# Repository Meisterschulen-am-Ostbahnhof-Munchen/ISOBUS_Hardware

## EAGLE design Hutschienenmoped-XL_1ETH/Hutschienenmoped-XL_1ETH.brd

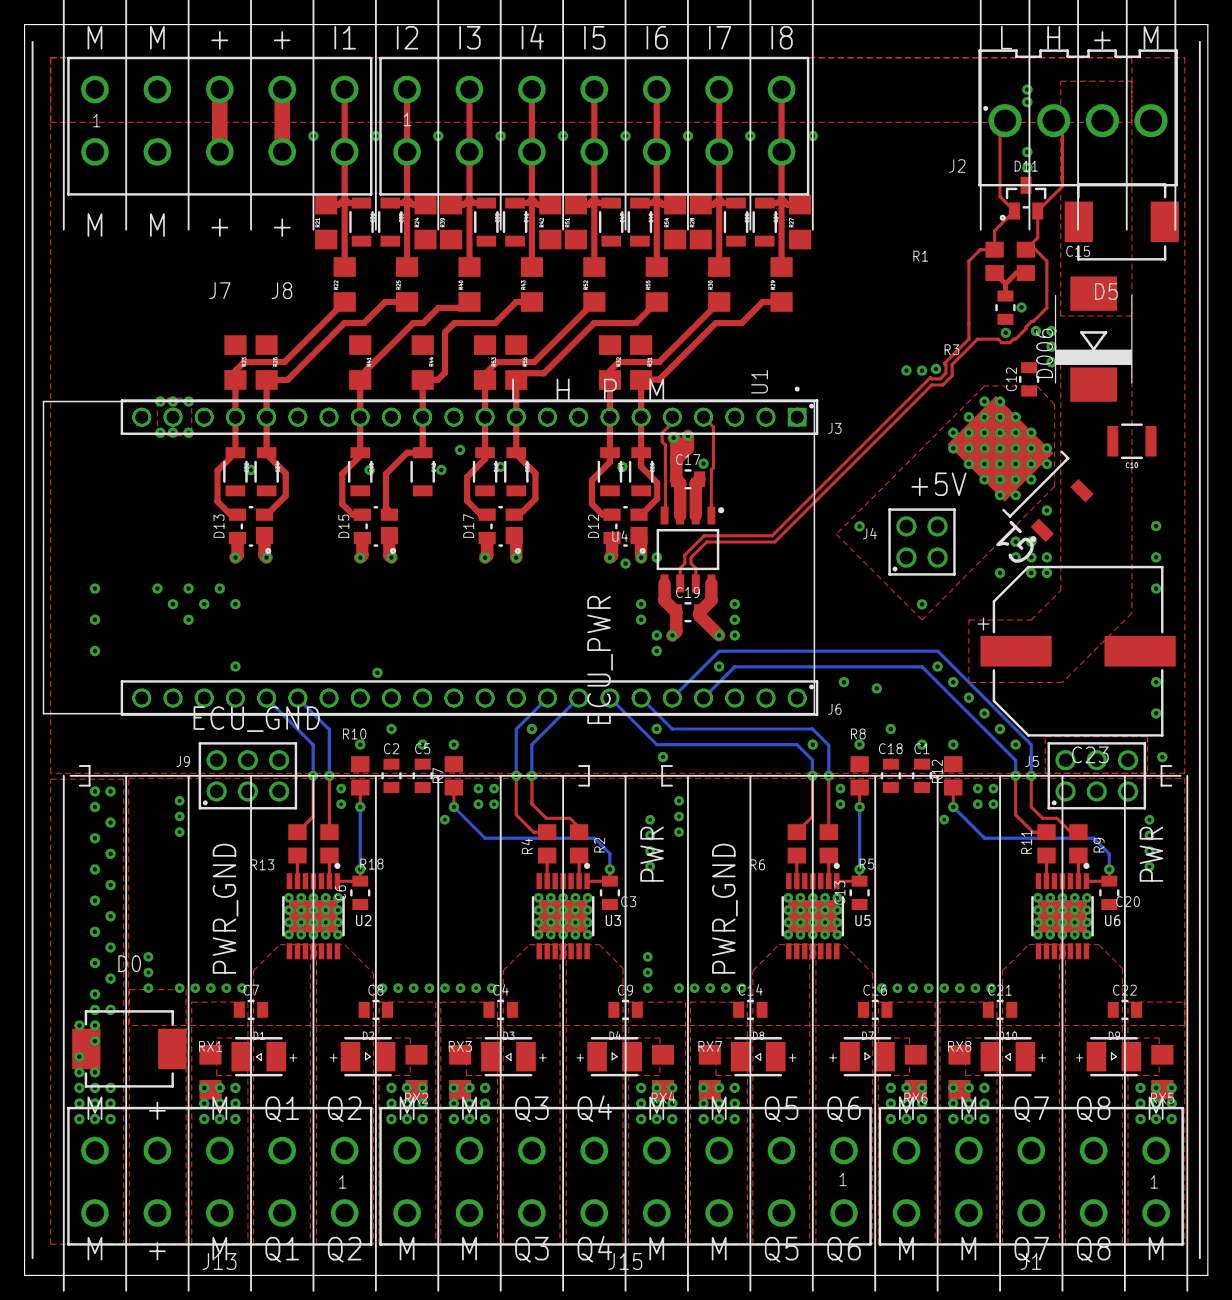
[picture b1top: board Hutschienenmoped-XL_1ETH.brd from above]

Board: 4 copper layers, 96.3 x 101.8 mm, 118 parts (0 on the bottom side), 65 nets.

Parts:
C1, C2, C3, C5, C6, C13, C17, C18, C19, C20: 100nF; WCAP-CSGP_0805_H0.8_R
C4, C7, C8, C9, C14, C16, C21, C22: 10nF; WCAP-CSGP_0805_H0.8_R
C10: 22uF; WCAP-CSGP_1210_H2.5
C12: 22uF; WCAP-CSGP_0805_H1.25_R
C15: 47nF; WCAP-CSGP_0805_H0.8_R
C23: 330 µF; WCAP-ASLI_12.5X14(DXL)
C24, C25, C26, C27, C31, C32, C33, C34, C39, C40, C41, C42, C47, C48, C49, C50: 100nF; WCAP-CSGP_1206_H0.8
D0, D5: 33V; WE-TVSP_DO-214AB_BIDIRECTIONAL
D1, D2, D3, D4, D7, D8, D9, D10: 150141VS73100; WL-SMTW_3528
D006: MBRS340T3; SMC
D11: 24Vdc; WE-TVS_SOT23-3L
D12, D13, D15, D17: 3.3Vdc; WE-TVS_SOT143-4L
G1: INF-PG-TO252-3-11_N
J1, J7, J13: 638207222005
J2: 645004114822
J3, J6: 61302211821
J4: 61300421121
J5, J9: 61300621121
J8: 638207222007
J15: 638207222008
R1, R3: 60R; R0805
R2, R4, R5, R6, R9, R11, R13, R18: 4k7; R0805
R7, R8, R10, R12: 47R; R0805
R21, R24, R27, R28, R39, R42, R51, R54: 1K2; R1206
R22, R25, R29, R30, R40, R43, R52, R55: 47K; R1206
R23, R26, R31, R32, R41, R44, R53, R56: 13K; R1206
RX1, RX2, RX3, RX4, RX5, RX6, RX7, RX8: 470Ohm; R1206
U1: ESP32-S3-DEVKITC-1-N8R2; XCVR_ESP32-S3-DEVKITC-1-N8R2
U2, U3, U5, U6: SOP65P600X115-15N-V
U4: TLE9250VSJ; SOIC127P602X173-8N-V

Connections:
+3V3: C19.1, D12.4, D13.4, D15.4, D17.4, U1.J1_1, U1.J1_2, U4.5
+5V: C12.2, C17.1, G1.2, J4.1, J4.2, J4.3, J4.4, U1.J1_21, U4.3
+6V: D7.1, RX6.1
AGNDU2: C6.2, R10.2, U2.1
AGNDU3: C3.2, R7.2, U3.1
AGNDU4: C13.2, R8.2, U5.1
AGNDU5: C20.2, R12.2, U6.1
CAN1_RXD: U1.J1_5, U4.4
CAN1_TXD: U1.J1_4, U4.1
CAN_N: D11.1, J2.1, R3.2, U4.6
CAN_P: D11.2, J2.2, R1.2, U4.7
CI1: C32.1, D13.3, R22.1, R23.2, U1.J1_19
CI2: C34.1, D13.2, R25.1, R26.2, U1.J1_18
CI3: C40.1, D15.3, R40.1, R41.2, U1.J1_15
CI4: C42.1, D15.2, R43.1, R44.2, U1.J1_13
CI5: C48.1, D17.3, R52.1, R53.2, U1.J1_11
CI6: C50.1, D17.2, R55.1, R56.2, U1.J1_10
CI7: C27.1, D12.3, R30.1, R32.2, U1.J1_7
CI8: C26.1, D12.2, R29.1, R31.2, U1.J1_6
ECU_GND: C1.2, C2.2, C5.2, C10.1, C12.1, C15.2, C17.2, C18.2, C19.2, C23.2, C24.2, C25.2, C26.2, C27.2, C31.2, C32.2, C33.2, C34.2, C39.2, C40.2, C41.2, C42.2, C47.2, C48.2, C49.2, C50.2, D5.1, D11.3, D12.1, D13.1, D15.1, D17.1, G1.1, J2.4, J7.1, J7.2, J7.A1, J7.A2, J9.2, J9.4, J9.6, R7.1, R8.1, R10.1, R12.1, R21.1, R23.1, R24.1, R26.1, R27.1, R28.1, R31.1, R32.1, R39.1, R41.1, R42.1, R44.1, R51.1, R53.1, R54.1, R56.1, U1.J1_22, U1.J3_1, U1.J3_21, U1.J3_22, U4.2, U4.8
ECU_PWR: D5.2, D006.A, J2.3, J5.2, J5.4, J5.6, J7.3, J7.4, J7.A3, J7.A4
I1: C31.1, J7.5, J7.A5, R21.2, R22.2
I2: C33.1, J8.1, J8.A1, R24.2, R25.2
I3: C39.1, J8.2, J8.A2, R39.2, R40.2
I4: C41.1, J8.3, J8.A3, R42.2, R43.2
I5: C47.1, J8.4, J8.A4, R51.2, R52.2
I6: C49.1, J8.5, J8.A5, R54.2, R55.2
I7: C25.1, J8.6, J8.A6, R28.2, R30.2
I8: C24.1, J8.7, J8.A7, R27.2, R29.2
unnamed: D4.1, RX4.1
unnamed: R2.2, U3.2
unnamed: C10.2, C23.1, D006.C, G1.3
unnamed: R4.2, U3.6
unnamed: R5.2, U5.2
unnamed: D2.1, RX2.1
unnamed: D1.1, RX1.2
unnamed: D3.1, RX3.2
unnamed: R18.2, U2.2
unnamed: R6.2, U5.6
unnamed: R9.2, U6.2
unnamed: R11.2, U6.6
unnamed: R13.2, U2.6
unnamed: D9.1, RX5.1
unnamed: C15.1, R1.1, R3.1
unnamed: D8.1, RX7.2
unnamed: D10.1, RX8.2
unnamed: J13.5, J13.A5
PWR: C1.1, C2.1, C3.1, C5.1, C6.1, C13.1, C18.1, C20.1, D0.2, J5.1, J5.3, J5.5, J13.4, J13.A4, U2.15, U3.15, U5.15, U6.15
PWR_GND: C4.1, C7.1, C8.2, C9.2, C14.1, C16.2, C21.1, C22.2, D0.1, J1.1, J1.4, J1.5, J1.A1, J1.A4, J1.A5, J9.1, J9.3, J9.5, J13.3, J13.A3, J15.3, J15.4, J15.7, J15.8, J15.A3, J15.A4, J15.A7, J15.A8, RX1.1, RX2.2, RX3.1, RX4.2, RX5.2, RX6.2, RX7.1, RX8.1
Q1: C7.2, D1.2, J13.2, J13.A2, U2.8, U2.9, U2.10
Q1C: R13.1, U1.J3_18
Q2: C8.1, D2.2, J13.1, J13.A1, U2.12, U2.13, U2.14
Q2C: R18.1, U1.J3_17
Q3: C4.2, D3.2, J15.6, J15.A6, U3.8, U3.9, U3.10
Q3C: R4.1, U1.J3_9
Q4: C9.1, D4.2, J15.5, J15.A5, U3.12, U3.13, U3.14
Q4C: R2.1, U1.J3_8
Q5: C14.2, D8.2, J15.2, J15.A2, U5.8, U5.9, U5.10
Q5C: R6.1, U1.J3_7
Q6: C16.1, D7.2, J15.1, J15.A1, U5.12, U5.13, U5.14
Q6C: R5.1, U1.J3_6
Q7: C21.2, D10.2, J1.3, J1.A3, U6.8, U6.9, U6.10
Q7C: R11.1, U1.J3_4
Q8: C22.1, D9.2, J1.2, J1.A2, U6.12, U6.13, U6.14
Q8C: R9.1, U1.J3_5

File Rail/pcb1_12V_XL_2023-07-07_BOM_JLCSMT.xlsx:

Comment | Designator | Footprint | JLCPCB Part #（optional）
BTS7030-2EPA | U2, U3, U5, U6 | SOP65P600X115-15N-V
100nF | C11 | WCAP-CSGP_0402
100nF | C1, C2, C3, C5, C6, C13, C17, C18, C19, C20 | WCAP-CSGP_0805_H0.8_R
100nF | C24, C25, C26, C27, C31, C32, C33, C34, C39, C40, C41, C42, C47, C48, C49, C50 | WCAP-CSGP_1206_H0.8
10nF | C4, C7, C8, C9, C14, C16, C21, C22 | WCAP-CSGP_0805_H0.8_R
13K | R23, R26, R31, R32, R41, R44, R53, R56 | R1206
150141VS73100 | D1, D2, D3, D4, D7, D8, D9, D10 | WL-SMTW_3528
1K2 | R21, R24, R27, R28, R39, R42, R51, R54 | R1206
22uF | C12 | WCAP-CSGP_0805_H1.25_R
22uF | C10 | WCAP-CSGP_1210_H2.5
24Vdc | D11 | WE-TVS_SOT23-3L
3.3Vdc | D12, D13, D15, D17 | WE-TVS_SOT143-4L
33V | D0, D5 | WE-TVSP_DO-214AB_BIDIRECTIONAL
470Ohm | RX1, RX2, RX3, RX4, RX5, RX6, RX7, RX8 | WRIS-KWKB_0612
47K | R22, R25, R29, R30, R40, R43, R52, R55 | R1206
47R | R7, R8, R10, R12 | R0805
47nF | C15 | WCAP-CSGP_0805_H0.8_R
4k7 | R2, R4, R5, R6, R9, R11, R13, R18 | R0805
60R | R1, R3 | R0805
B4P-VH | X2 | B4P-VH
TLE4270-2D-INF-PG-TO252-5-11_L_1 | G1 | INF-PG-TO252-5-11_L_1PRIMARY
TLE9250VSJ | U4 | SOIC127P602X173-8N-V

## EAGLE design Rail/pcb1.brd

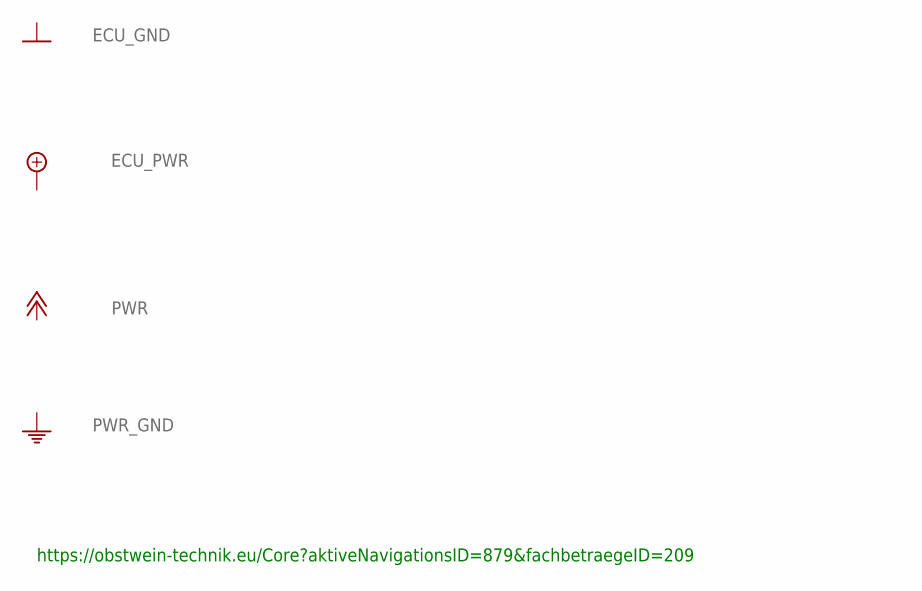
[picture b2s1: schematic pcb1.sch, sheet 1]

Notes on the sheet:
https://obstwein-technik.eu/Core?aktiveNavigationsID=879&fachbetraegeID=209

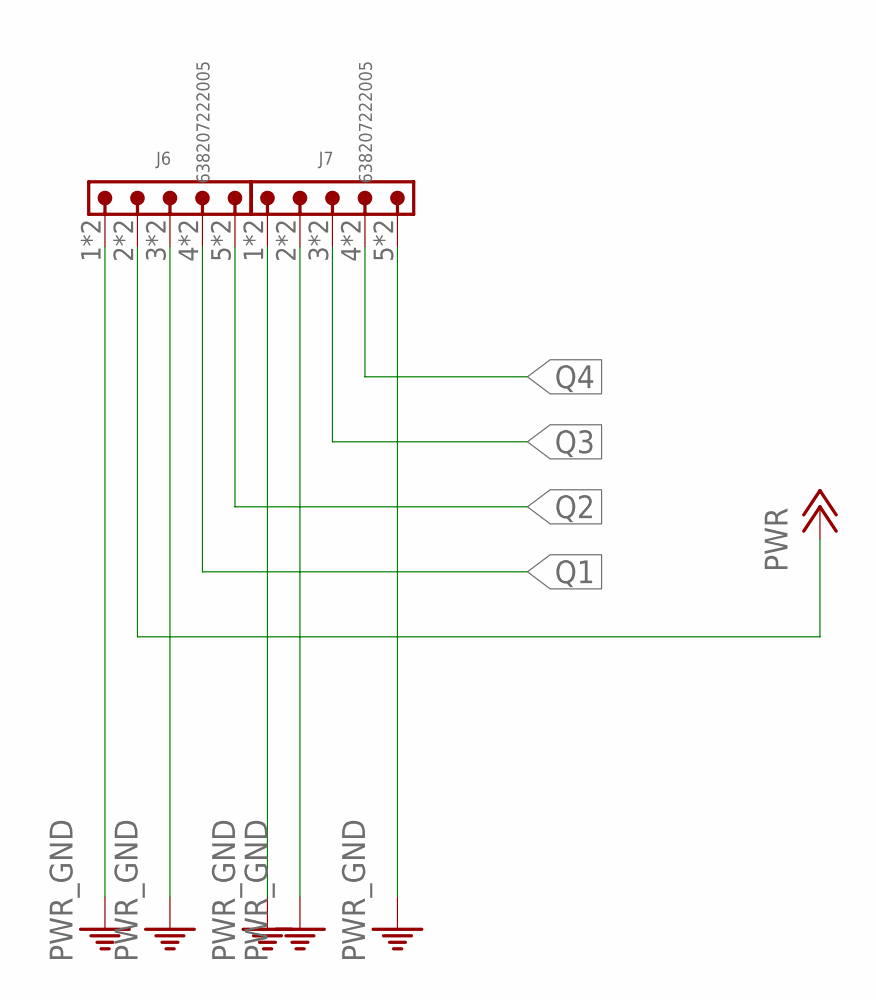
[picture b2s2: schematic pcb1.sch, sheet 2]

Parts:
J6, J7: 638207222005

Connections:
PWR: J6.2, J6.A2 (2); also elsewhere on the board
PWR_GND: J6.1, J6.3, J6.A1 (1), J6.A3 (3), J7.1, J7.2, J7.5, J7.A1 (1), J7.A2 (2), J7.A5 (5); also elsewhere on the board
Q1: J6.4, J6.A4 (4); also elsewhere on the board
Q2: J6.5, J6.A5 (5); also elsewhere on the board
Q3: J7.3, J7.A3 (3); also elsewhere on the board
Q4: J7.4, J7.A4 (4); also elsewhere on the board

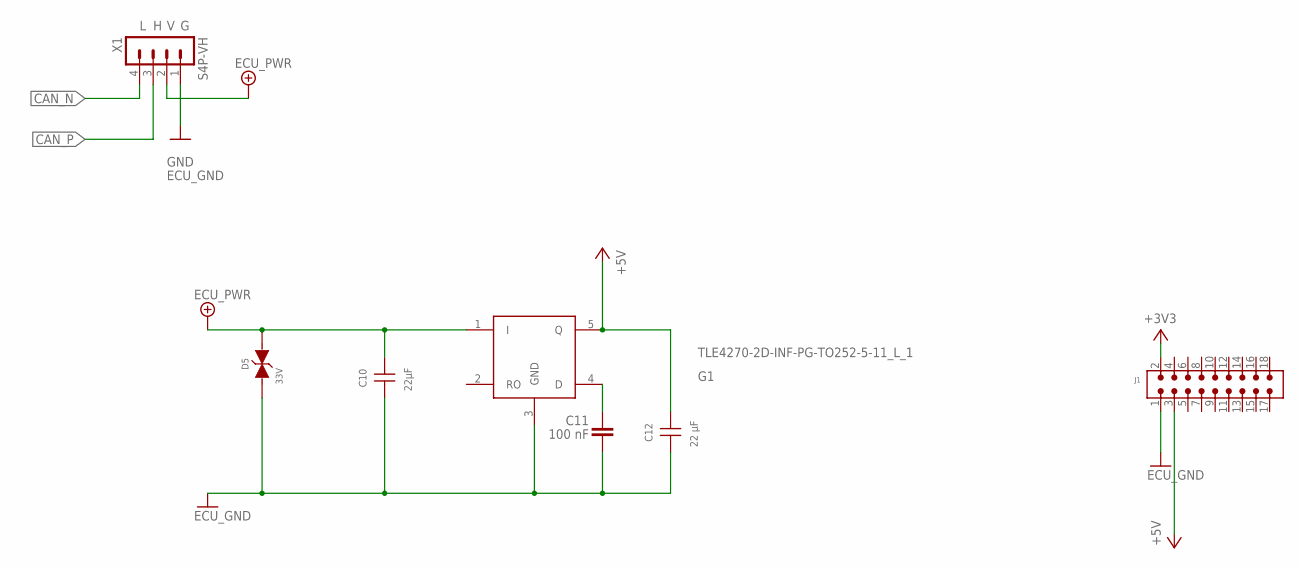
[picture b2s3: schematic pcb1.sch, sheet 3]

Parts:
C10: 22µF; WCAP-CSGP_1210_H2.5
C11: 100 nF; WCAP-CSGP_0402
C12: 22 µF; WCAP-CSGP_0805_H1.25_R
D5: 33V; WE-TVSP_DO-214AB_BIDIRECTIONAL
G1: TLE4270-2D-INF-PG-TO252-5-11_L_1; INF-PG-TO252-5-11_L_1PRIMARY
J1: 6130XX21121_61301821121; 61301821121
X1: S4P-VH

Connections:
+3V3: J1.2; also elsewhere on the board
+5V: C12.2, G1.5 (Q), J1.3; also elsewhere on the board
CAN_N: X1.4; also elsewhere on the board
CAN_P: X1.3; also elsewhere on the board
ECU_GND: C10.1, C11.2, C12.1, D5.1, G1.3 (GND), J1.1, X1.1; also elsewhere on the board
ECU_PWR: C10.2, D5.2, G1.1 (I), X1.2; also elsewhere on the board
unnamed: C11.1, G1.4 (D)

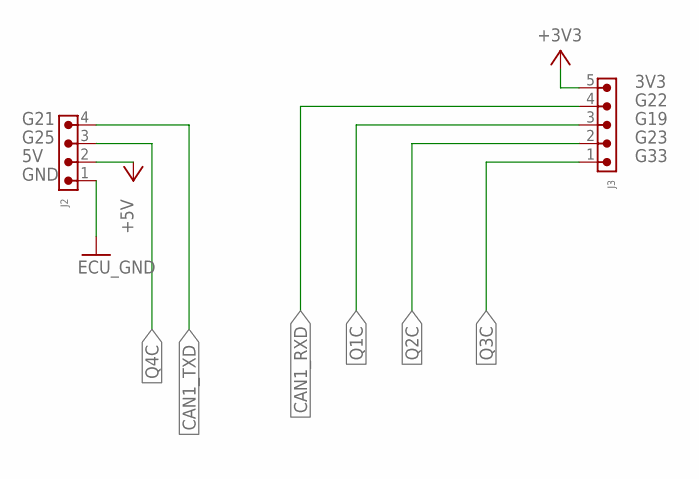
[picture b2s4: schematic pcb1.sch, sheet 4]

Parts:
J2: 6130XX11121_61300411121; 61300411121
J3: 6130XX11121_61300511121; 61300511121

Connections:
+3V3: J3.5; also elsewhere on the board
+5V: J2.2; also elsewhere on the board
CAN1_RXD: J3.4; also elsewhere on the board
CAN1_TXD: J2.4; also elsewhere on the board
ECU_GND: J2.1; also elsewhere on the board
Q1C: J3.3; also elsewhere on the board
Q2C: J3.2; also elsewhere on the board
Q3C: J3.1; also elsewhere on the board
Q4C: J2.3; also elsewhere on the board

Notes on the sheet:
GND
G25
G21
G33
G23
G19
G22
3V3

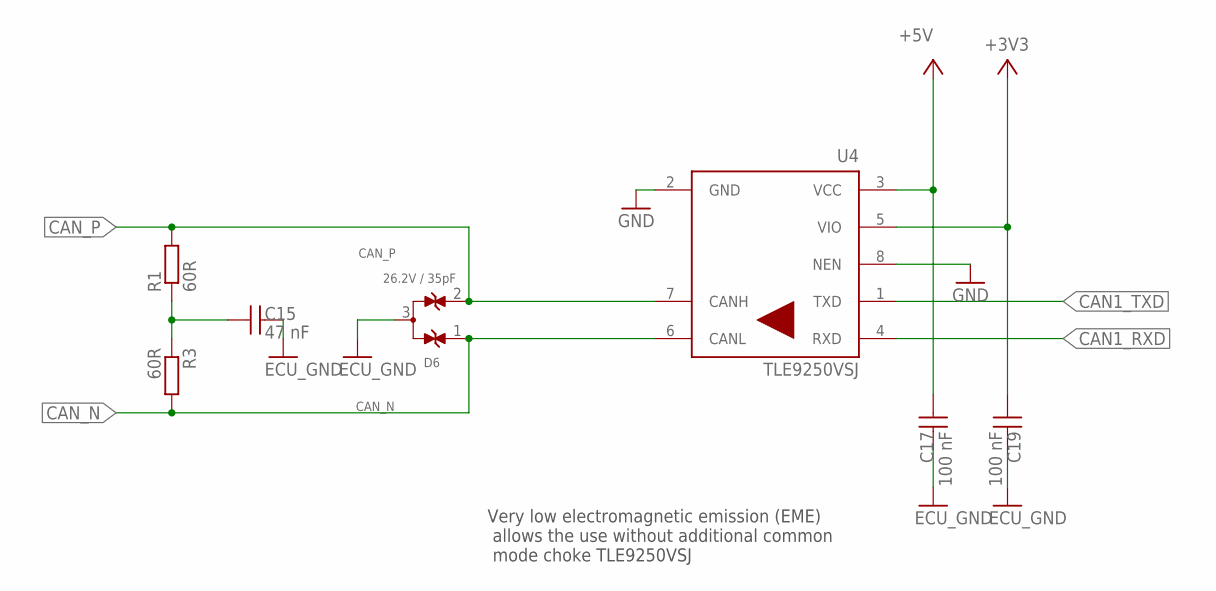
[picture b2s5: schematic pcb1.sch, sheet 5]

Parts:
C15: 47 nF; WCAP-CSGP_0805_H0.8_R
C17, C19: 100 nF; WCAP-CSGP_0805_H0.8_R
D6: 26.2V / 35pF; WE-TVS_SOT23-3L
R1, R3: 60R; R0805
U4: TLE9250VSJ; SOIC127P602X173-8N-V

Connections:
+3V3: C19.1, U4.5 (VIO); also elsewhere on the board
+5V: C17.1, U4.3 (VCC); also elsewhere on the board
CAN1_RXD: U4.4 (RXD); also elsewhere on the board
CAN1_TXD: U4.1 (TXD); also elsewhere on the board
CAN_N: D6.1, R3.2, U4.6 (CANL); also elsewhere on the board
CAN_P: D6.2, R1.2, U4.7 (CANH); also elsewhere on the board
ECU_GND: C15.2, C17.2, C19.2, D6.3, U4.2 (GND), U4.8 (NEN); also elsewhere on the board
unnamed: C15.1, R1.1, R3.1

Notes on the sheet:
Very low electromagnetic emission (EME) allows the use without additional common mode choke TLE9250VSJ

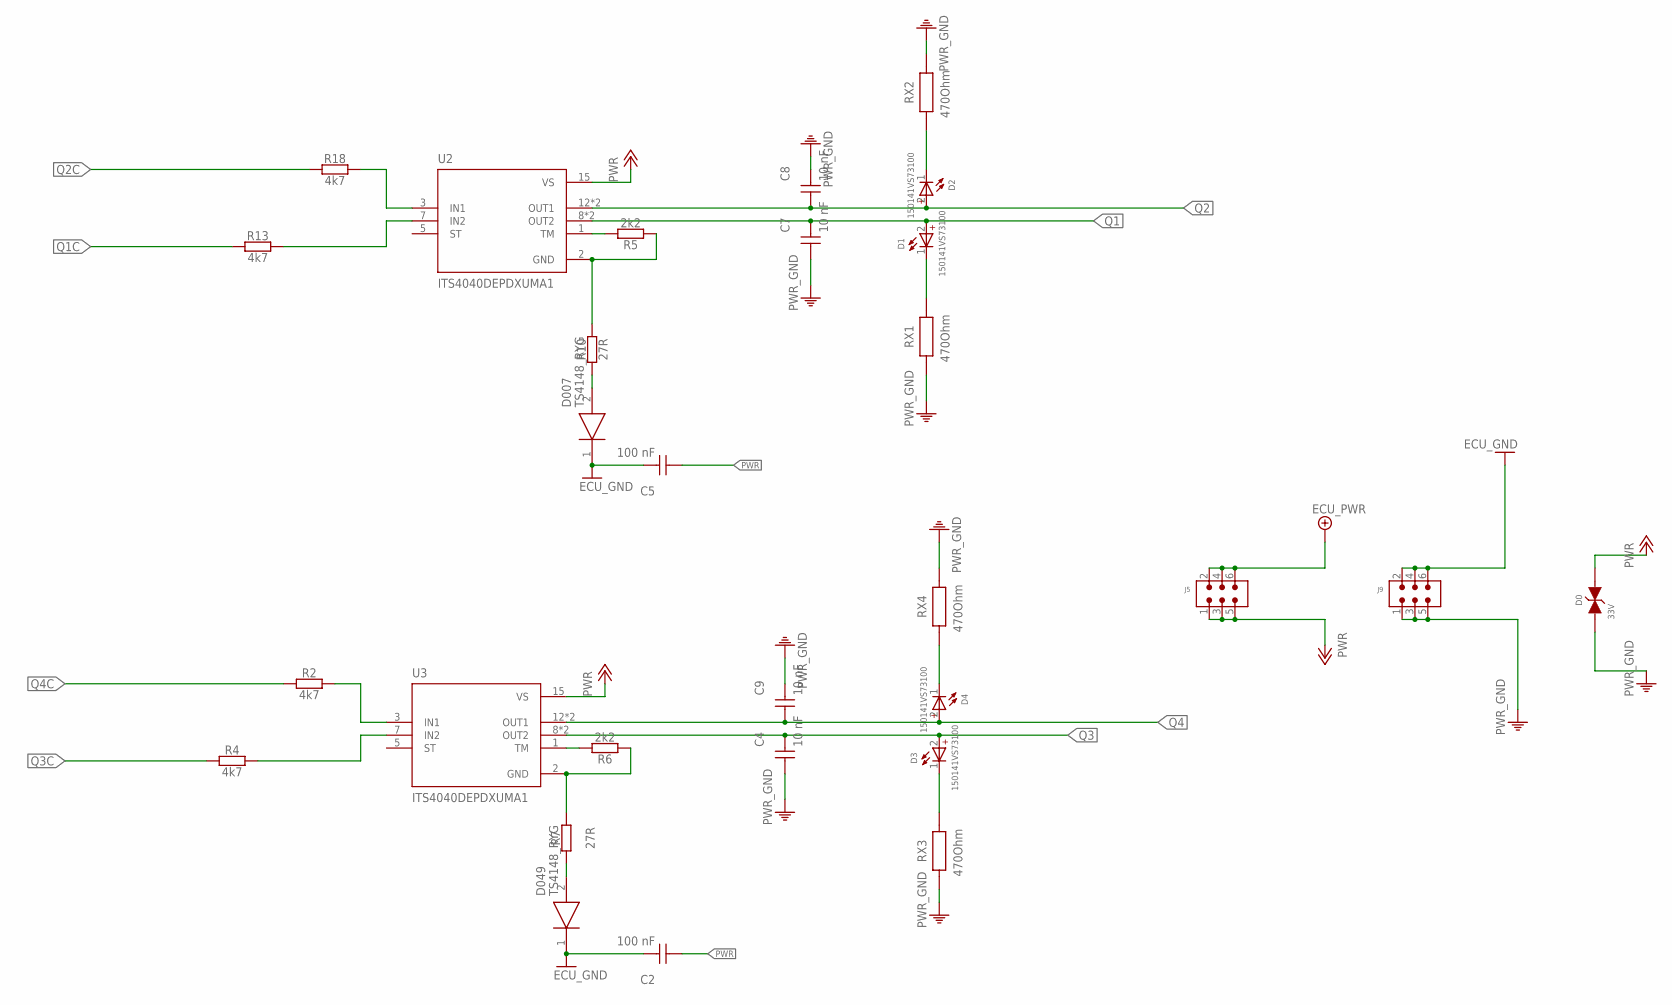
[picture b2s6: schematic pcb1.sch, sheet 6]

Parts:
C2, C5: 100 nF; WCAP-CSGP_0805_H0.8_R
C4, C7, C8, C9: 10 nF; WCAP-CSGP_0805_H0.8_R
D0: 33V; WE-TVSP_DO-214AB_BIDIRECTIONAL
D1, D2, D3, D4: 150141VS73100; WL-SMTW_3528
D007, D049: TS4148_RYG; DIOC2012X95N
J5, J9: 6130XX21121_61300621121; 61300621121
R2, R4, R13, R18: 4k7; R0805
R5, R6: 2k2; R0805
R7, R10: 27R; R0805
RX1, RX2, RX3, RX4: 470Ohm; WRIS-KWKB_0612
U2, U3: ITS4040DEPDXUMA1; SOP65P600X115-15N

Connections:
ECU_GND: C2.2, C5.2, D007.1 (K), D049.1 (K), J9.2, J9.4, J9.6; also elsewhere on the board
ECU_PWR: J5.2, J5.4, J5.6; also elsewhere on the board
unnamed: D4.1 (-), RX4.1
unnamed: R2.2, U3.3 (IN1)
unnamed: R6.2, U3.1 (TM)
unnamed: R4.2, U3.7 (IN2)
unnamed: R5.2, U2.1 (TM)
unnamed: D2.1 (-), RX2.1
unnamed: D1.1 (-), RX1.2
unnamed: D3.1 (-), RX3.2
unnamed: R18.2, U2.3 (IN1)
unnamed: D049.2 (A), R7.1
unnamed: D007.2 (A), R10.1
unnamed: R6.1, R7.2, U3.2 (GND)
unnamed: R13.2, U2.7 (IN2)
unnamed: R5.1, R10.2, U2.2 (GND)
PWR: C2.1, C5.1, D0.2, J5.1, J5.3, J5.5, U2.15 (VS), U3.15 (VS); also elsewhere on the board
PWR_GND: C4.1, C7.1, C8.2, C9.2, D0.1, J9.1, J9.3, J9.5, RX1.1, RX2.2, RX3.1, RX4.2; also elsewhere on the board
Q1: C7.2, D1.2 (+), U2.8 (OUT2), U2.10 (OUT2); also elsewhere on the board
Q1C: R13.1; also elsewhere on the board
Q2: C8.1, D2.2 (+), U2.12 (OUT1), U2.14 (OUT1); also elsewhere on the board
Q2C: R18.1; also elsewhere on the board
Q3: C4.2, D3.2 (+), U3.8 (OUT2), U3.10 (OUT2); also elsewhere on the board
Q3C: R4.1; also elsewhere on the board
Q4: C9.1, D4.2 (+), U3.12 (OUT1), U3.14 (OUT1); also elsewhere on the board
Q4C: R2.1; also elsewhere on the board

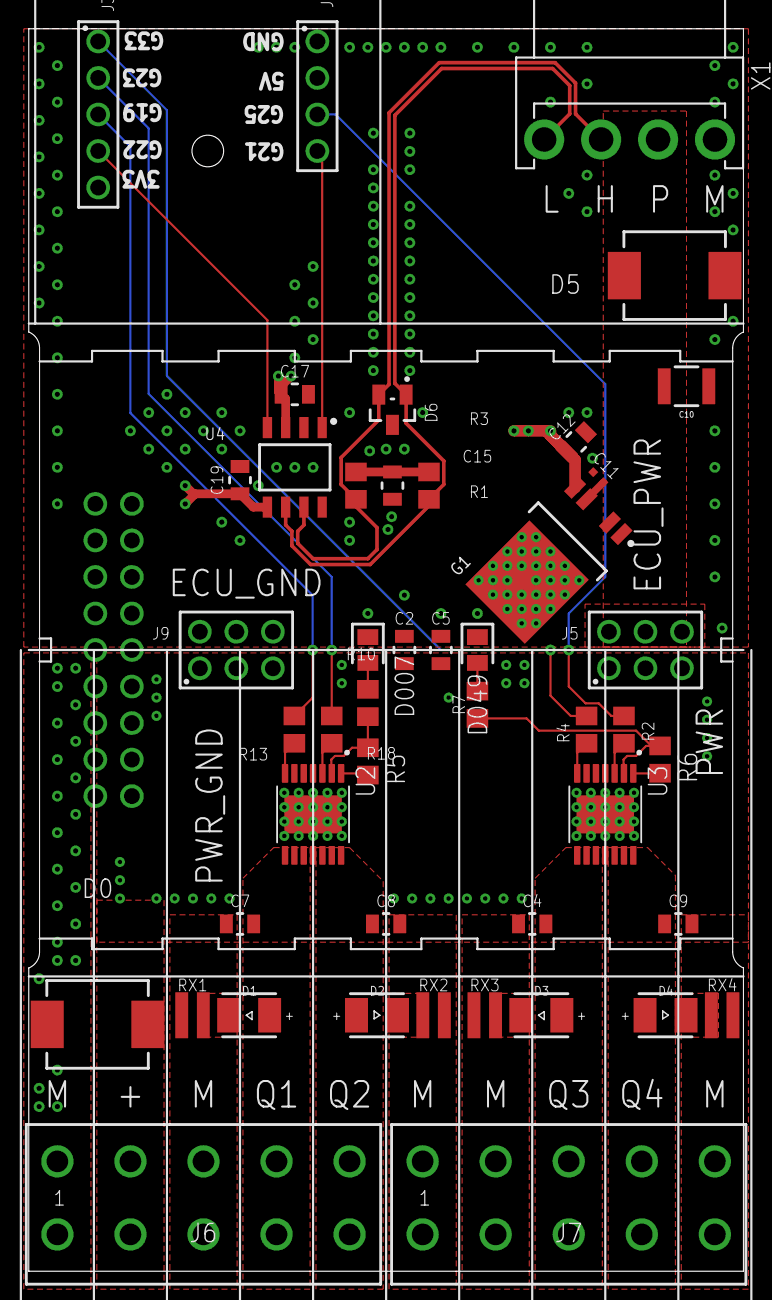
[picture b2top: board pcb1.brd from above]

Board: 4 copper layers, 49.7 x 86.4 mm, 47 parts (1 on the bottom side), 34 nets.

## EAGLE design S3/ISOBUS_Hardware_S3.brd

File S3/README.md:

### 3D

Look: https://a360.co/35uHefM

Look: https://a360.co/35xwNb1

Look: https://a360.co/3hpeZ4w

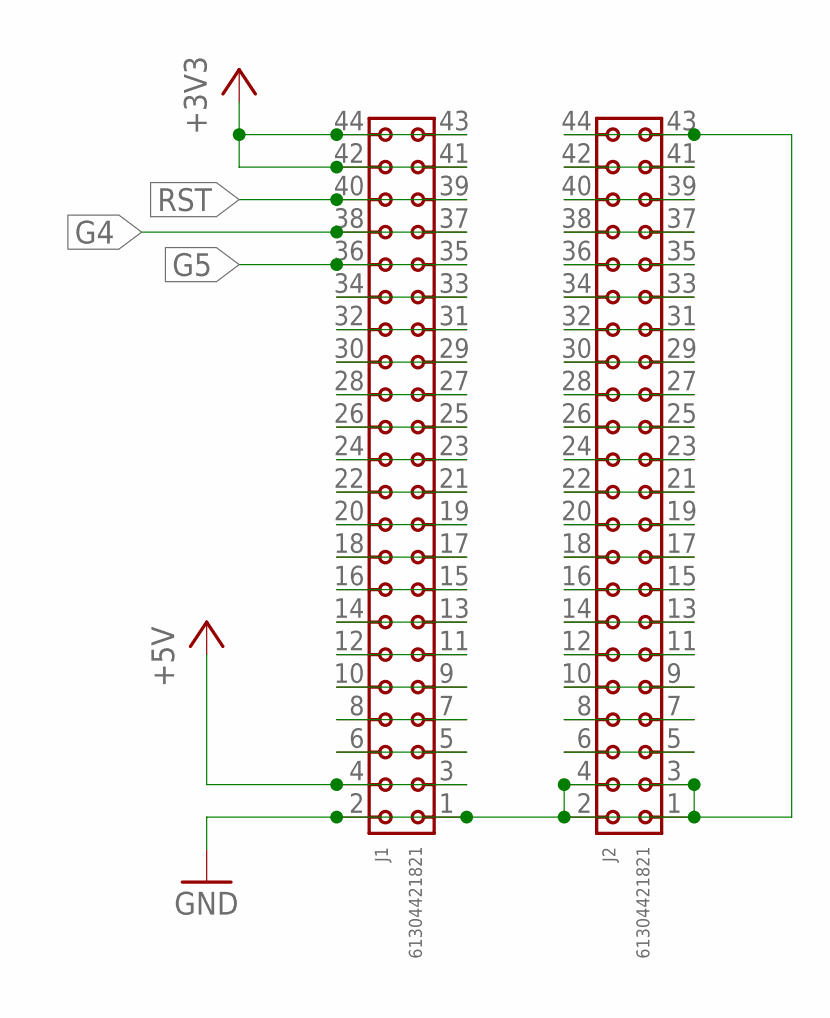
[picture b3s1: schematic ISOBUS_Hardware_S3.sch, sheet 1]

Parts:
J1, J2: 61304421821

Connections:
+3V3: J1.41, J1.42, J1.43, J1.44; also elsewhere on the board
+5V: J1.3, J1.4; also elsewhere on the board
G4: J1.37, J1.38; also elsewhere on the board
G5: J1.35, J1.36; also elsewhere on the board
GND: J1.1, J1.2, J2.1, J2.2, J2.3, J2.4, J2.43, J2.44; also elsewhere on the board
unnamed: J1.33, J1.34
unnamed: J1.31, J1.32
unnamed: J1.29, J1.30
unnamed: J1.27, J1.28
unnamed: J1.25, J1.26
unnamed: J1.23, J1.24
unnamed: J1.21, J1.22
unnamed: J1.19, J1.20
unnamed: J1.17, J1.18
unnamed: J1.15, J1.16
unnamed: J1.13, J1.14
unnamed: J1.11, J1.12
unnamed: J1.9, J1.10
unnamed: J1.7, J1.8
unnamed: J1.5, J1.6
unnamed: J2.5, J2.6
unnamed: J2.7, J2.8
unnamed: J2.9, J2.10
unnamed: J2.11, J2.12
unnamed: J2.13, J2.14
unnamed: J2.15, J2.16
unnamed: J2.17, J2.18
unnamed: J2.19, J2.20
unnamed: J2.21, J2.22
unnamed: J2.23, J2.24
unnamed: J2.25, J2.26
unnamed: J2.27, J2.28
unnamed: J2.29, J2.30
unnamed: J2.31, J2.32
unnamed: J2.33, J2.34
unnamed: J2.35, J2.36
unnamed: J2.37, J2.38
unnamed: J2.39, J2.40
unnamed: J2.41, J2.42
RST: J1.39, J1.40

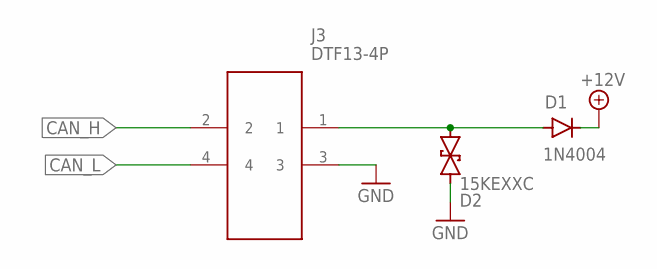
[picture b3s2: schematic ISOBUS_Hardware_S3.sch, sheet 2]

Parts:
D1: 1N4004; DO-41
D2: 15KEXXC; CB429-17
J3: DTF13-4P; DTF134P

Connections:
+12V: D1.C; also elsewhere on the board
CAN_H: J3.2; also elsewhere on the board
CAN_L: J3.4; also elsewhere on the board
GND: D2.A (1), J3.3; also elsewhere on the board
unnamed: D1.A, D2.C (2), J3.1

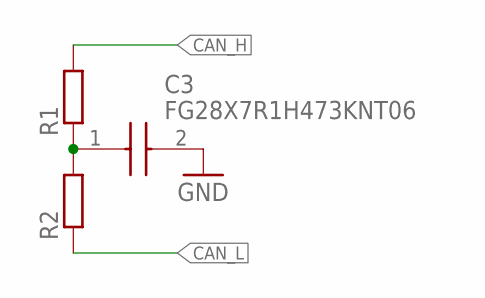
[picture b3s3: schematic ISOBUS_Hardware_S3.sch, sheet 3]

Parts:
C3: FG28X7R1H473KNT06; FG28
R1, R2: R-EU_0204/7; 0204/7

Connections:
CAN_H: R1.2; also elsewhere on the board
CAN_L: R2.1; also elsewhere on the board
GND: C3.2; also elsewhere on the board
unnamed: C3.1, R1.1, R2.2

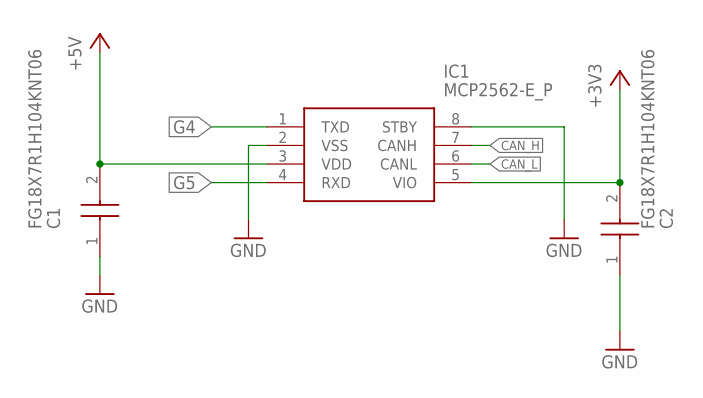
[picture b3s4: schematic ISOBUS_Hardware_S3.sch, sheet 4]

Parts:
C1, C2: FG18X7R1H104KNT06; FG18C0G1H101JNT06
IC1: MCP2562-E_P; DIP781W56P254L950H533Q8N

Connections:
+3V3: C2.2, IC1.5 (VIO); also elsewhere on the board
+5V: C1.2, IC1.3 (VDD); also elsewhere on the board
CAN_H: IC1.7 (CANH); also elsewhere on the board
CAN_L: IC1.6 (CANL); also elsewhere on the board
G4: IC1.1 (TXD); also elsewhere on the board
G5: IC1.4 (RXD); also elsewhere on the board
GND: C1.1, C2.1, IC1.2 (VSS), IC1.8 (STBY); also elsewhere on the board

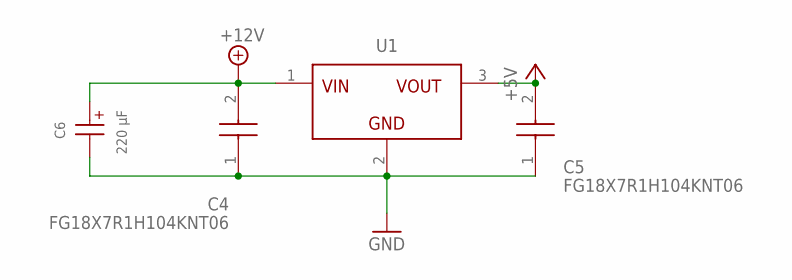
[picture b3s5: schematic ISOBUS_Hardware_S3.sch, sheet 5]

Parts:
C4, C5: FG18X7R1H104KNT06; FG18C0G1H101JNT06
C6: 220 µF; WCAP-ATG8_6.3X11(DXL)
U1: MAGI³C-FDSM_SIP-3_173010542_173XXXX42; MAGI³C-FDSM_173XXXX42

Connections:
+5V: C5.2, U1.3 (VOUT); also elsewhere on the board
+12V: C4.2, C6.1 (+), U1.1 (VIN); also elsewhere on the board
GND: C4.1, C5.1, C6.2 (-), U1.2 (GND); also elsewhere on the board

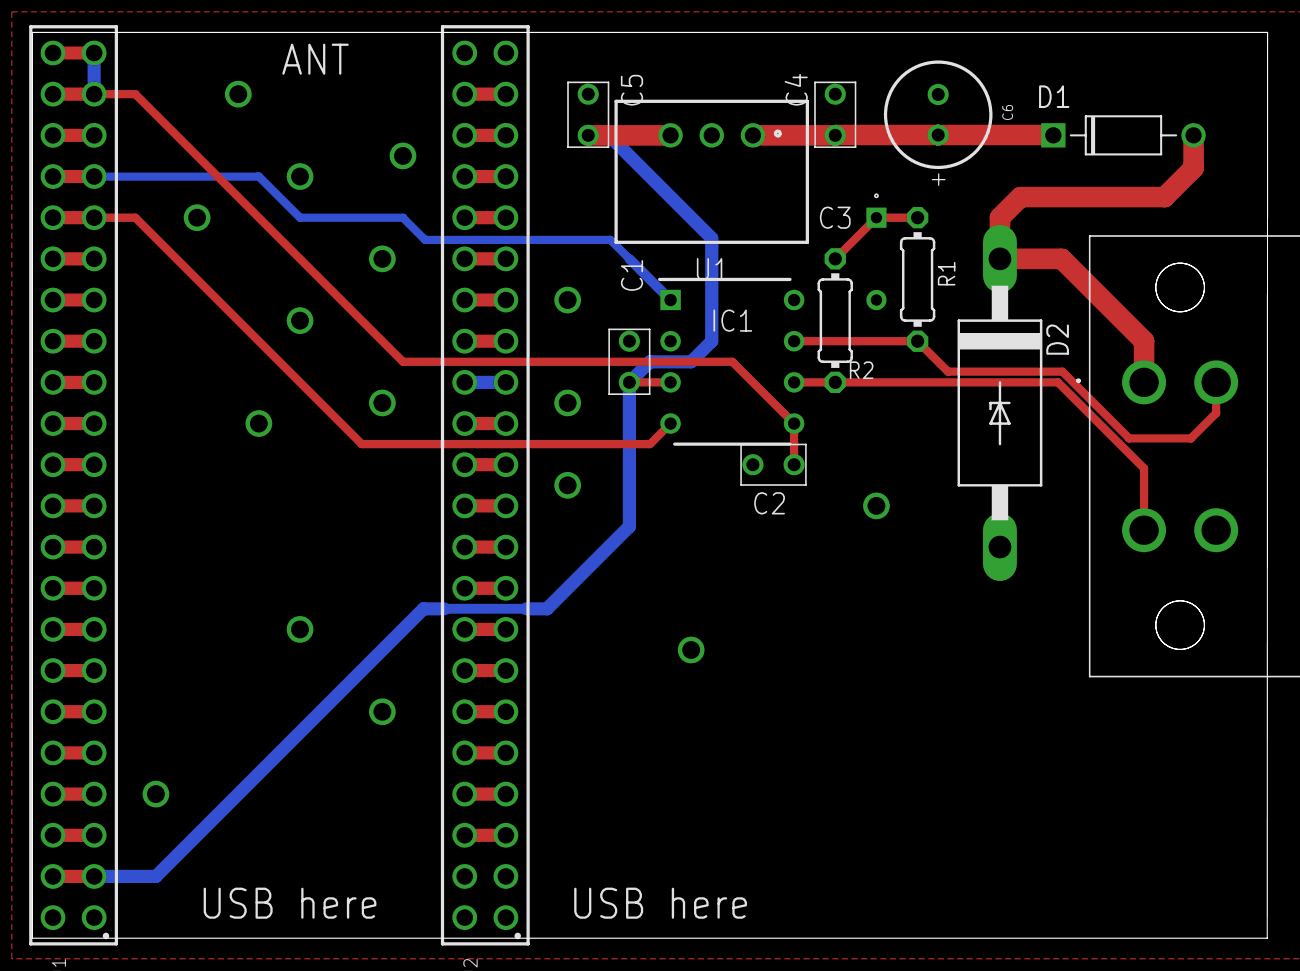
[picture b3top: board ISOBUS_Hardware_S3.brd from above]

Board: 2 copper layers, 76.2 x 55.9 mm, 15 parts (0 on the bottom side), 45 nets.

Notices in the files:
parts and their libraries:
Wurth_EMC Components_WE-TVSP: Copyright: Würth Elektronik
